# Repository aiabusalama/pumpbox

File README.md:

# REISBOT Pump Guard

A small box that keeps a solar-powered water pump alive. Rust on a Raspberry Pi Zero W.

## The problem

The pump is a 138 V, 1.5 kW DC brushless submersible (110–150 V range, 11 A max). Its own controller card
is destroyed above 150 V. The array is three GSE-HC455 panels in series: 150.9 V open-circuit at 25 °C, and
climbing toward 165 V on a cold morning — exactly the voltage present at sunrise, before any current flows.
That killed the first controller card. The second time it could not be repaired.

## What the box does

- Watches the array voltage and current every few milliseconds (PZEM-017 over RS-485).
- Keeps the contactor open until the array has settled inside the safe window (95–145 V), and drops it
  again on over-voltage, under-voltage, over-current, a dry well, or loss of contact with the meter.
- Waits, re-checks that the voltage is steady (about 15 s), and restarts by itself.
- Runs the pump from the water levels: a level relay in the well, another in the tank.
- Shows everything on a 20×4 LCD, one status light (blinking = ready, solid = running, two flashes =
  too high, three = too low) and a phone dashboard over its own Wi-Fi hotspot.

## Parts

| Part | Role |
|---|---|
| Raspberry Pi Zero W | the brain, runs `pumpd` |
| PZEM-017 + 50 A shunt | volts, amps, watts on the pump line |
| Schneider contactor | switches the 150 V DC pump line |
| 5 V relay module | drives the contactor coil from the Pi |
| HLK-10M24 | 143 V → 24 V for the contactor coil |
| 5 V / 3 W supply | the Pi |
| 12 V converter | feeds the two level relays |
| 2 × SSRC-04 level relays | well and tank levels — sold for 220 V AC, bypassed to run on 12 V DC (two jumper wires) |
| 20×4 I²C LCD, mode switch, START / STOP buttons | the front panel |

## Repo layout

- `rust/` — `pumpd`, the controller: state machine, PZEM-017 meter, front panel, LCD, watchdog, fail-safe,
  web dashboard. `rust/src/bin/` holds two bench tools (`failprobe`, `wdtest`).
- `kicad/level/` — the level-sensor board (schematic, PCB, etch transfers, drill file, wire-link map); `kicad/render/`
  shows the finished board; `kicad/BOM.txt` is the sourcing list.
- `hotspot/` — the Pi's Wi-Fi hotspot: setup script, captive-portal responder, watchdog units.
- `fritzing/`, `qet/` — wiring sketch and electrical diagram.
- `docs/` — enclosure layout and wiring pages; `DESIGN.md` and `BUILD.md` — design notes and build guide.

## Disclaimer

This is a personal hobby project, built for one farm and shared as-is. It is not a product, it is not certified,
and it is not affiliated with or endorsed by any employer or manufacturer. It switches 150 V DC, which can injure
or kill: if you copy any of it, you take full responsibility for your own installation, and you should have a
qualified electrician check it. No warranty of any kind — see the licence.

## Licence

MIT

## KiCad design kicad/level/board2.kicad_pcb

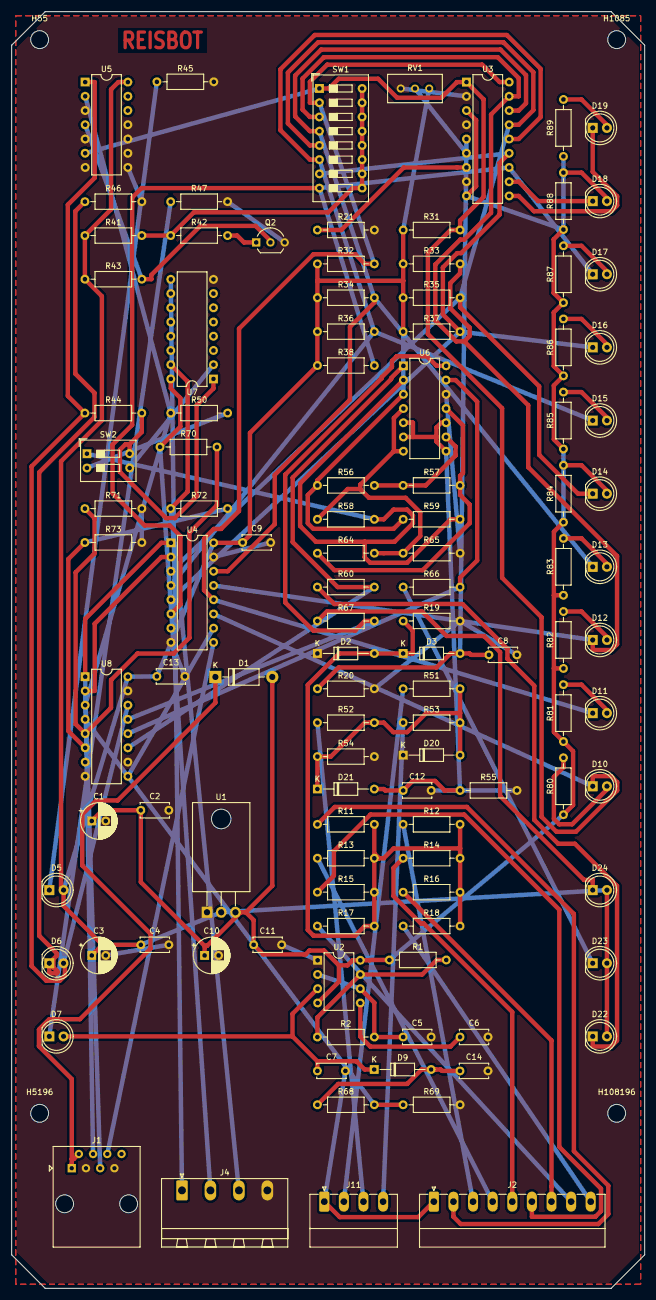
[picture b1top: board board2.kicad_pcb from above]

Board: 2 copper layers, 113.0 x 227.9 mm, 115 parts (0 on the bottom side), 78 nets.

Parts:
C1: 100u/16V; CP_Radial_D6.3mm_P2.50mm
C2, C4, C5, C7, C8, C9, C11, C12, C13, C14: 100n; C_Disc_D5.0mm_W2.5mm_P5.00mm
C3: 10u/16V; CP_Radial_D6.3mm_P2.50mm
C6: 10n; C_Disc_D5.0mm_W2.5mm_P5.00mm
C10: 100u/10V; CP_Radial_D6.3mm_P2.50mm
D1: 1N5819; D_DO-41_SOD81_P10.16mm_Horizontal
D2, D3, D20, D21: BAT85; D_DO-35_SOD27_P10.16mm_Horizontal
D5: PWR green; LED_D5.0mm
D6: PUMP red; LED_D5.0mm
D7: EXC yellow; LED_D5.0mm
D9: 1N4148; D_DO-35_SOD27_P10.16mm_Horizontal
D10: TANK 1 red; LED_D5.0mm
D11: TANK 2 red; LED_D5.0mm
D12: TANK 3 red; LED_D5.0mm
D13: TANK 4 yellow; LED_D5.0mm
D14: TANK 5 yellow; LED_D5.0mm
D15: TANK 6 green; LED_D5.0mm
D16: TANK 7 green; LED_D5.0mm
D17: TANK 8 green; LED_D5.0mm
D18: TANK 9 green; LED_D5.0mm
D19: TANK 10 green; LED_D5.0mm
D22: WELL 1 red; LED_D5.0mm
D23: WELL 2 yellow; LED_D5.0mm
D24: WELL 3 green; LED_D5.0mm
H55, H1085, H5196, H108196: MountingHole_3.2mm_M3_DIN965
J1: CAT5 TO PI; RJ45_Amphenol_54602-x08_Horizontal
J2: PROBES; PhoenixContact_MC_1,5_9-G-3.5_1x09_P3.50mm_Horizontal
J4: PUMP / VALVE; PhoenixContact_MSTBA_2,5_4-G-5,08_1x04_P5.08mm_Horizontal
J11: WELL PROBES; PhoenixContact_MC_1,5_4-G-3.5_1x04_P3.50mm_Horizontal
Q2: BC547; TO-92_Inline_Wide
R1, R31, R32, R33, R34, R35, R36, R37, R38, R41, R42, R43, R59: 10k; R_Axial_DIN0207_L6.3mm_D2.5mm_P10.16mm_Horizontal
R2, R44, R50: 4k7; R_Axial_DIN0207_L6.3mm_D2.5mm_P10.16mm_Horizontal
R11, R12: 390k; R_Axial_DIN0207_L6.3mm_D2.5mm_P10.16mm_Horizontal
R13: 330k; R_Axial_DIN0207_L6.3mm_D2.5mm_P10.16mm_Horizontal
R14, R51: 270k; R_Axial_DIN0207_L6.3mm_D2.5mm_P10.16mm_Horizontal
R15: 200k; R_Axial_DIN0207_L6.3mm_D2.5mm_P10.16mm_Horizontal
R16, R53, R69: 150k; R_Axial_DIN0207_L6.3mm_D2.5mm_P10.16mm_Horizontal
R17: 110k; R_Axial_DIN0207_L6.3mm_D2.5mm_P10.16mm_Horizontal
R18: 68k; R_Axial_DIN0207_L6.3mm_D2.5mm_P10.16mm_Horizontal
R19, R54, R68, R70, R72: 100k; R_Axial_DIN0207_L6.3mm_D2.5mm_P10.16mm_Horizontal
R20, R55, R58: 1M; R_Axial_DIN0207_L6.3mm_D2.5mm_P10.16mm_Horizontal
R21: 1k2; R_Axial_DIN0207_L6.3mm_D2.5mm_P10.16mm_Horizontal
R45, R46: 1k; R_Axial_DIN0207_L6.3mm_D2.5mm_P10.16mm_Horizontal
R47: 2k2; R_Axial_DIN0207_L6.3mm_D2.5mm_P10.16mm_Horizontal
R52: 220k; R_Axial_DIN0207_L6.3mm_D2.5mm_P10.16mm_Horizontal
R56: 56k; R_Axial_DIN0207_L6.3mm_D2.5mm_P10.16mm_Horizontal
R57: 18k; R_Axial_DIN0207_L6.3mm_D2.5mm_P10.16mm_Horizontal
R60, R66, R67, R80, R81, R82, R83, R84, R85, R86, R87, R88, R89: 470; R_Axial_DIN0207_L6.3mm_D2.5mm_P10.16mm_Horizontal
R64: 16k; R_Axial_DIN0207_L6.3mm_D2.5mm_P10.16mm_Horizontal
R65: 12k; R_Axial_DIN0207_L6.3mm_D2.5mm_P10.16mm_Horizontal
R71, R73: 15k; R_Axial_DIN0207_L6.3mm_D2.5mm_P10.16mm_Horizontal
RV1: 10k; Potentiometer_Bourns_3296W_Vertical
SW1: TARGET LEVEL; SW_DIP_SPSTx08_Slide_9.78x22.5mm_W7.62mm_P2.54mm
SW2: WELL / VALVE EN; SW_DIP_SPSTx02_Slide_9.78x7.26mm_W7.62mm_P2.54mm
U1: AP1117-33; TO-220-3_Horizontal_TabDown
U2: TLC555; DIP-8_W7.62mm
U3: LM3914; DIP-18_W7.62mm
U4, U8: 74HC165; DIP-16_W7.62mm
U5: 4013; DIP-14_W7.62mm
U6: LM339; DIP-14_W7.62mm
U7: ULN2003A; DIP-16_W7.62mm

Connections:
+3V3: C3.1, C4.1, C9.1, C13.1, D5.2, D22.2, D23.2, D24.2, R31.1, R32.1, R33.1, R34.1, R35.1, R36.1, R37.1, R38.1, R41.1, R43.1, R56.1, R59.1, RV1.1, U1.2, U4.16, U5.14, U6.3, U8.16
+5V: C1.1, C2.1, C10.1, C11.1, D1.2, R1.1, R80.1, R81.1, R82.1, R83.1, R84.1, R85.1, R86.1, R87.1, R88.1, R89.1, U1.3, U2.4, U2.8, U3.3, U3.9
COIL_V: J4.1, U7.9
DET: C8.1, D3.2, R20.1, U3.5
EXC: C7.2, J2.1, J11.1
EXC_OK: R68.2, R69.1, U8.4
EXC_RAW: C14.1, D9.2, R68.1
GND: C1.2, C2.2, C3.2, C4.2, C5.2, C6.2, C8.2, C9.2, C10.2, C11.2, C12.2, C13.2, C14.2, D2.1, D20.1, J1.3, J1.7, J4.4, Q2.3, R19.2, R20.2, R21.2, R45.2, R46.2, R47.2, R54.2, R55.2, R65.2, R69.2, R71.2, R73.2, RV1.3, U1.1, U2.1, U3.2, U3.4, U3.8, U4.8, U4.15, U5.3, U5.5, U5.7, U5.8, U5.9, U5.10, U5.11, U6.12, U7.8, U8.8, U8.10, U8.15
L1: D10.1, R31.2, SW1.1, U3.1, U4.11, U5.6
L2: D11.1, R32.2, SW1.2, U3.18, U4.12
L3: D12.1, R33.2, SW1.3, U3.17, U4.13
L4: D13.1, R34.2, SW1.4, U3.16, U4.14
L5: D14.1, R35.2, SW1.5, U3.15, U4.3
L6: D15.1, R36.2, SW1.6, U3.14, U4.4
L7: D16.1, R37.2, SW1.7, U3.13, U4.5
L8: D17.1, R38.2, SW1.8, U3.12, U4.6
L9: D18.1, U3.11
L10: D19.1, U3.10
LA1: D10.2, R80.2
LA2: D11.2, R81.2
LA3: D12.2, R82.2
LA4: D13.2, R83.2
LA5: D14.2, R84.2
LA6: D15.2, R85.2
LA7: D16.2, R86.2
LA8: D17.2, R87.2
LA9: D18.2, R88.2
LA10: D19.2, R89.2
LADDER: D2.2, D3.1, R11.2, R12.2, R13.2, R14.2, R15.2, R16.2, R17.2, R18.2, R19.1
LEDW0: D22.1, R60.1
LEDW1: D23.1, R66.1
LEDW2: D24.1, R67.1
LED_EXC: D7.1, R47.1
LED_PMP: D6.1, R46.1
LED_PWR: D5.1, R45.1
OSC_C: C6.1, U2.5
OSC_D: R1.2, R2.1, U2.7
OSC_OUT: C7.1, D7.2, D9.1, U2.3
OSC_T: C5.1, R2.2, U2.2, U2.6
P1: J2.2, R11.1
P2: J2.3, R12.1
P3: J2.4, R13.1
P4: J2.5, R14.1
P5: J2.6, R15.1
P6: J2.7, R16.1
P7: J2.8, R17.1
P8: J2.9, R18.1
PUMP: D6.2, R44.1, U5.1, U8.14
PUMP_EN: R44.2, SW2.4, U7.1
PUMP_N: R50.1, U5.2, U8.3
PUMP_OUT: J4.2, R70.1, U7.16
PUMP_SNS: R70.2, R71.1, U8.5
Q2B: Q2.1, R42.2
REF: R21.1, U3.7
RHI_SET: RV1.2, U3.6
SCLK: J1.5, U4.2, U8.2
SDATA: J1.6, U4.9
SLOAD: J1.4, U4.1, U8.1
TARGET: R41.2, R42.1, SW1.9, SW1.10, SW1.11, SW1.12, SW1.13, SW1.14, SW1.15, SW1.16
TGT_HI: Q2.2, R43.2, U5.4
U8Q7: U4.10, U8.9
VIN: D1.1, J1.1, J1.2
VLV_EN: SW2.3, U7.2
VLV_GATE: R50.2, SW2.2
VLV_OUT: J4.3, R72.1, U7.15
VLV_SNS: R72.2, R73.1, U8.6
W1: J11.2, R51.1
W2: J11.3, R52.1
W3: J11.4, R53.1
WDET: C12.1, D21.2, R55.1, U6.5, U6.6, U6.8, U6.10
WELL1: R60.2, U6.1, U8.11
WELL2: R66.2, U6.13, U8.12
WELL3: R67.2, U6.14, U8.13
WELL_OK: R58.2, R59.2, SW2.1, U6.2
WLADDER: D20.2, D21.1, R51.2, R52.2, R53.2, R54.1
WREF1: R58.1, R64.2, R65.1, U6.4, U6.7
WREF2: R57.2, R64.1, U6.11
WREF3: R56.2, R57.1, U6.9
